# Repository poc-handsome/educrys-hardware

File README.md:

# educrys-hardware

Subfolders contain the documentation for [mechanical](/mechanical-design) (TODO) and [electronic](/electronic-design) (TODO) design of EduCrys setup for the users who want to build or adapt it by themselves.

The sections below provide information for users who have received a ready-to-use setup.

## Packing

While most electronic components of EduCrys are enclosed in a robust metallic box, many sensors and other parts need careful packing to avoid damage during transport. The pictures below show an example of such packing. The final package has dimensions of 60x41x23 cm and weight of 13.3 kg.

## Transport without packing

If the EduCrys setup is transported in the partly-assembled state, the following safety measures are recommended:

- Disconnect the rotation motor, detach the seed holder, wind the pulling wire on the main pulley and fix it with a tape
- Disconnect the camera and detach it from the magic arm
- Tape the crucible and camera cable to the main body to prevent motion
- Pack the seed holder and camera separately

## List of components

### Main components

- Main body with all connectors detached, except the camera cable, which is taped on the right wall. Two M6 screws are left in the profiles on both sides.
- Main stand with the pulling motor and weight cell. The pulling wire is wound and taped on the motor roll.
- Second stand with the fan and the small sensor box. The infrared sensor and LED should be protected with bubble wrap.
- Seed holder with a rotation motor in a bubble wrap bag. Small S-shaped hook to attach the seed holder to the pulling wire.
- Aluminum crucible with solid tin (99.9%), in a bubble wrap bag, should not move around in the transport box.

### Sensors and cables

- Raspberry Pi camera with a cover, attached to a magic arm, all inside a bubble wrap
- 1x PT100 and 2x thermocouple sensors with about 1.5 m wire length
- Raspberry Pi keyboard incl. USB cable and mouse, gamepad
- HDMI monitor cable, power cable

### Tools

- 30 cm metallic ruler
- Small spoon and small metal blow to be used when removing oxide layer
- 3 Inbus keys for seed holder, for opening main body, and for mounting both vertical profiles
- Nylon wire, which can be used temporarily if the steel wire of the seed holder breaks
- Warning sign for hot surfaces

### Raw material

- About 1 mm thick tin crystal, which can be used as seed
- About 1 mm thick copper wire, which can be used as seed
- (Tin pellets with 99.9% purity)

### Not included
- Protective glasses when working close to the crucible. **The hot liquid metal may splash if something falls into the melt!**
- Protective gloves when touching the hot crucible, for example, to adjust its position.
- Monitor
- Power strip

## Assembling the setup

### Mechanical

- Place the main body on a table with the logo on the front
- Attach the main stand on the left profile with a M6 screw, close to the front. Connect the motor and weight cell cables.
- Attach the fan stand on the right profile with a M6 screw, close to the back. Connect the fan and sensor cables.
- Guide the pulling wire over 3 pulleys from the pulling motor to the weight cell. Insert a hook in the loop at the wire end. Keep the wire tightened, otherwise it will unwind itself from the pulley on the motor axis.
- Hang the seed holder on the hook. The tilt of the seed holder should remain adjustable in two perpendicular directions.
- Attach the cable with two pins to the rotation motor. The polarity is not important. Keep the free length of this cable sufficient during the motion of the seed holder. This cable prevents the seed holder from rotating, but it should not pull it away from the vertical axis.
- Place the crucible on the hotplate. Check that the seed holder is in the middle of the crucible. Adjust the main stand position if necessary.

### Sensors and cables

- Attach the magic arm with camera on the right profile, close to the front. Carefully pull out the camera cable from the slit in the right wall. Insert the cable end into the connector at the back of the camera with the conducting pins towards the board. Push the black connector part upwards to fix the cable.
- Insert the PT100 sensor in a horizontal borehole and one thermocouple in a vertical borehole of the crucible. Both sensor cables should be bound together to prevent the PT100 sliding out of the hole. **This would lead to strong overheating of the crucible during temperature-controlled heating!**
- The second thermocouple could be used to measure ambient air, melt, or some parts inside the main body.
- Connect the keyboard with the red USB cable to the socket in the right wall. Connect the mouse and the gamepad to the keyboard. The USB ports in the keyboard can be also used to attach USB flash memory for data transfer.
- Connect a monitor to the HDMI socket in the right wall.
- Attach the power cable at the back of the main body. **Raspberry Pi starts as soon as power is connected! Always use the shutdown function in the Menu before disconnecting the power to avoid data loss.**
- If necessary, a network cable can be attached directly to the Raspberry Pi board through an opening in the back wall. Remove the screws and carefully pull the back wall for about 5 cm to access Raspberry Pi. **The network socket in the back wall can be only used for the sensor box.**

### Clock 

- Check the system clock after the log in. Newer EduCrys setups have a hardware clock with battery backup, while others rely on synchronization over network.
- The following steps are required to install an external hardware clock, see also [raspberry-pi-geek.de](https://www.raspberry-pi-geek.de/ausgaben/rpg/2015/03/echtzeituhr-modul-ds3231-sorgt-fuer-genaue-zeitangaben/2/) 
  - Update system time: `sudo date -s "19 May 2025 18:00:00" `
  - Attach the hardware clock to the I2C bus and find the address (e.g. 68): `sudo i2cdetect -y 1`
  - Configure the system to use the hardware clock (use the address from above) and add this line also to /etc/rc.local: `echo ds3231 0x68 | sudo tee /sys/class/i2c-adapter/i2c-1/new_device`
  - Synchronize the hardware clock with system time: `sudo hwclock -w`
  - Disable synchronization over network: `sudo update-rc.d ntp disable`   `sudo update-rc.d fake-hwclock disable`   `sudo timedatectl set-ntp false`

The final setup should look like this.

## Acknowledgements

[This project](https://poc-handsome.github.io/) has received funding from the European Research Council (ERC) under the 
European Union’s Horizon Europe framework programme for research and innovation (grant agreement No. 101122970).

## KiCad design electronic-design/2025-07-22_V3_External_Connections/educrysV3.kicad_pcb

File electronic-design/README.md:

## E01 PCB

### Layout of the PCB

Design files for KiCad (8.0.0) are here: [KiCad](https://github.com/poc-handsome/educrys-hardware/tree/main/electronic-design/E01/KiCad)

The following improvements have not been implemented yet:
- Separate pin header for the clock module
- Larger screw terminal for the connection between main PCB and sensor PCB
- Avoid risk of short circuit when soldering capacitors

### Soldering

Main PCB with soldered parts, top and bottom views:

Sensor PCB with soldered parts, top and bottom views:

Remarks:
- The connection between the main board and sensor board must be cut 
- For all screw terminals the holes are oriented to the rim of the board 
- A small 2 mm gap should be left between the 100 uF capacitor to avoid short circuit 
- Resitor values are not printed correctly on the board, use closes E12 values
- All flux residues should be cleaned from both board sides, e.g. using Kontaktchemie LR

### Modules

PCB after mounting the modules:

Remarks:

- First solder pin headers [E04H3] on the bottom of all modules [E03T2 etc.]. Make short breaks to avoid overheating the chip
- Solder screw terminals on the top of modules [E03T5, E03T2, E03W2, E03C]. The holes are oriented to the center of the board for [E03T5, E03W2] and to the rim of the board for [E03T2, E03C]
- Solder a female header on the top of the module [E03C] (4 pins on the left) and connect the module [E03D] there
- All flux residues should be cleaned from both board sides, e.g. using Kontaktchemie LR
- The modules will be fastened later to the PCB with a 10 mm spacer and two M2.5 screws. M3 screws are too big!

## E02 Wiring diagram

Schematic of the connections using the parts given below:

(pic)

Photo of the final wiring

(pic)

Remarks:

## E03 Devices: sensors, actuators

Prices are given per one piece in EUR incl. VAT. 

| Part  | Description                             | Use               | Price | Vendor/Link              | Datasheet | 
|-------|-----------------------------------------|-------------------|-------|--------------------------|-----------|
| E03H  | Hotplate, Severin KP 1092               | Crucible heating  | 27.99 | [Conrad/704233](https://www.conrad.de/de/p/severin-kp-1092-1092-kochplatte-704233.html?searchType=SearchRedirect)       |           |
| E03P1 | Stepper, Nema-17 1:20                   | Crystal pulling   | 56.90 | [Conrad/2355877](https://www.conrad.de/de/p/joy-it-schrittmotor-nema17-07gm-0-44-nm-1-68-a-wellen-durchmesser-8-mm-2355877.html?searchType=SearchRedirect)        |           |
| E03P2 | Motor driver IC, DRV8834                | Stepper motor     | 8.24  | [Exptech/80-2134](https://exp-tech.de/products/pololu-drv8834-low-voltage-stepper-motor-driver-carrier)     |           |
| E03R1 | DC motor 1000:1                         | Seed rotation     | 12.95 | [Conrad/1289388](https://www.conrad.de/de/p/sol-expert-g1000-micro-getriebemotor-g-1000-metallzahnraeder-1-1000-2-18-u-min-1289388.html?searchType=SearchRedirect)      |           |
| E03R2 | Motor driver IC, DRV8838                | DC motor          | 4.10  | [Exptech/80-2990](https://exp-tech.de/products/pololu-drv8838-single-brushed-dc-motor-driver-carrier)      |           |
| E03F1 | Fan, 120 mm, 5V                         | Crystal cooling   | 35.61 | [Conrad/816459971](https://www.conrad.de/de/p/noctua-nf-f12-5v-pwm-fan-1-pack-brun-120-mm5-v-pwm-0-75-w-0-15-a-93-4-816459971.html?searchType=SearchRedirect)    |           |
| E03W1 | Weight cell, 1 kg                       | Crystal weight    | 39.37 | [Conrad/2104290](https://www.conrad.de/de/p/sauter-ck-1-0p1-ck-1-0p1-messzelle-ck-p1-4-2104290.html?searchType=SearchRedirect)      |           |
| E03W2 | Weight cell driver IC, HX711            | Weight cell       | 9.86  | [Digikey/1568-1436-ND](https://www.digikey.de/de/products/detail/sparkfun-electronics/13879/6202732?s=N4IgTCBcDaIIwFYBsAOAtHALAZiWgcgCIgC6AvkA)     |           |
| E03T1 | Thermal sensor PT100, 3x150 mm, 500 °C  | Temperature sensor | 142.87 | [RS/397-1315](https://de.rs-online.com/web/p/widerstands-temperatursensoren/3971315?searchId=d1256e21-5988-4aaf-8b94-83c79a26ba8f)             |           |
| E03T2 | PT100 driver IC, MAX31865               | Temperature sensor | 12.82 | [Digikey/1528-3328-ND](https://www.digikey.de/de/products/detail/adafruit-industries-llc/3328/6562952)    |           |
| E03T4 | 2x Thermocouple, Type K, 1x250 mm, 750 °C | Temperature sensor | 47.36 | [RS/787-7706](https://de.rs-online.com/web/p/thermoelemente/7877706?searchId=9bbca203-3abb-4fba-a2c3-11345d2f288b)       |           |
| E03T5 | Thermocouple driver IC, MAX31856        | Temperature sensor | 17.98  | [Digikey/1528-1772-ND](https://www.digikey.de/de/products/detail/adafruit-industries-llc/3263/6227009?s=N4IgTCBcDaIIwFYwA4C0cDsGyoHIBEQBdAXyA)    |           |
| E03C  | Current sensor, INA219                  | Motor current     | 8.53   | [Digikey/1528-904-ND](https://www.digikey.de/de/products/detail/adafruit-industries-llc/904/5353628?s=N4IgTCBcDaIIwFYwA4C0BOADAFlQOQBEQBdAXyA)      |           |
| E03A  | Air sensor, SHT31                       | Air temperature, humidity | 11.96 | [Digikey/1528-2857-ND](https://www.digikey.de/de/products/detail/adafruit-industries-llc/2857/5804106?s=N4IgTCBcDaIIYBM4DMBOBXAlgFwAQGUAJAFQGYBGEAXQF8g) |           |
| E03I  | IR sensor, MLX90640                     | Hotplate temperature | 30.28 | [Digikey/MLX90640ESF-BAB-000-TU-ND](https://www.digikey.de/de/products/detail/melexis-technologies-nv/MLX90640ESF-BAB-000-TU/8638464?s=N4IgTCBcDaILIBkAaBOADANgCxoKIGUAxAWgCEBBU4tG4gFQFViA5AERAF0BfIA) |           |
| E03D  | Real time clock, DS3231                 | Raspberry Pi time backup | 15.0  | [Digikey/1528-3013-ND](https://www.digikey.de/de/products/detail/adafruit-industries-llc/3013/5875808) |           |
| E03O1 | RPi camera                              | Optical camera | 51.90 | [Welectron/RP3-102610](https://www.welectron.com/Offizielle-Raspberry-Pi-HQ-Camera)        |           |
| E03O2 | Camera lens 8-50 mm                     | Optical camera | 42.90 | [Welectron/WS9-018245](https://www.welectron.com/Waveshare-18245-8-50mm-Zoom-Lens-for-Pi)        |           |

## E04 Electrical components

Prices are given per one piece in EUR incl. VAT. In some cases SETS with a larger number of parts are given.

| Part  | Description                             | Use               | Price | Vendor/Link              | Datasheet | 
|-------|-----------------------------------------|-------------------|-------|--------------------------|-----------|
| E04S1 | 2x Power socket                         | SSR box           | 4.79  | [Conrad/2484787](https://www.conrad.de/de/p/as-schwabe-45084-einbau-steckdose-grau-2484787.html?searchType=SearchRedirect)  |  |
| E04S2 | Solid state relais                      | SSR box           | 74.52 | [RS/491-4947](https://de.rs-online.com/web/p/halbleiterrelais/4914947)  |  |
| E04R1 | Raspberry Pi 4 B (4 GB)                 |                   | 57.90 | [Welectron/RP1-141400](https://www.welectron.com/Raspberry-Pi-4-B-4-GB)  |  |
| E04R2 | SD card 64GB                            | Raspberry Pi      | 6.9   | [Welectron/SD1-200644](https://www.welectron.com/SanDisk-SDSQUAB-064G-GN6MA-Ultra-microSD-Speicherkarte-64-GB-140-MB-s)  |  |
| E04R3 | Heatsink                                | Raspberry Pi      | 1.3   | [Welectron/409151](https://www.welectron.com/Raspberry-Pi-Kuehlkoerpersatz)  |  |
| E04R4 | Power supply 5V, 3A                     | Raspberry Pi      | 7.5   | [Welectron/408024-012](https://www.welectron.com/Offizielles-Raspberry-Pi-4-Steckernetzteil-USB-C-51V-3A-weiss-EU)  |  |
| E04R5 | Keyboard + mouse                        | Raspberry Pi      | 27.90 | [Welectron/409483-002](https://www.welectron.com/Offizielle-Raspberry-Pi-Tastatur-Maus-Kombination-rot-weiss-DE)  |  |
| E04R6 | Gamepad                                 | Raspberry Pi      | 4.99  | [Conrad/1954771](https://www.conrad.de/de/p/joy-it-gamepad-snes-design-gamepad-raspberry-pi-universal-grau-1954771.html?searchType=SearchRedirect)  |  |
| E04E1 | SET: Metal film resistors               | PCB               | 46.65 | [Reichelt/METALL E 12](https://www.reichelt.de/de/de/shop/produkt/metallschichtwiderstandssortiment_e12-12049)  |  |
| E04E2 | SET: Foil capacitors                    | PCB               | 83.50 | [Reichelt/SORTIMENT 100](https://www.reichelt.de/de/de/shop/produkt/sortimentsbox_folienkondensatoren_rm_5mm-19263)  |  |
| E04E3 | 4x Capacitor 100 uF                     | PCB               | 1.29  | [Conrad/1179727](https://www.conrad.de/de/p/panasonic-16sepc100m-elektrolyt-kondensator-radial-bedrahtet-2-5-mm-100-f-16-v-dc-20-o-x-h-6-3-mm-x-6-mm-1-st-1179727.html)  |  |
| E04E4 | Buzzer                                  | PCB               | 0.99  | [Reichelt/KXG1205C](https://www.reichelt.de/de/de/shop/produkt/indikator_85db_2300_hz_5_v-360852)  |  |
| E04E5 | 2x Transistor KC337                     | PCB               | 0.02  | [Reichelt/BC 337-16](https://www.reichelt.de/de/de/shop/produkt/bipolartransistor_npn_45v_0_8a_0_625w_to-92-4985)  |  |
| E04E6 | White LED                               | Sensor box        | 0.5   | [Conrad/180754](https://www.conrad.de/de/p/nichia-nspw300ds-sel-b2v-w-led-bedrahtet-weiss-rund-3-mm-15000-mcd-20-20-ma-3-2-v-180754.html)  |  |
| E04H1 | 3x Female header precision, 2.54 mm, 1x36 | PCB             | 3.79  | [Conrad/733779-VQ](https://www.conrad.de/de/p/mpe-garry-buchsenleiste-praezision-anzahl-reihen-1-polzahl-je-reihe-36-115-1-036-0-mtf-xs0-1-1-st-733779.html)  |  | 
| E04H2 | 2x Female header precision, 2.54 mm, 2x10 | PCB             | 2.79  | [Conrad/733843-VQ](https://www.conrad.de/de/p/mpe-garry-buchsenleiste-praezision-anzahl-reihen-2-polzahl-je-reihe-10-115-3-020-0-mtf-xs0-1-st-733843.html)  |  |
| E04H3 | 2x Pin header, 2.54 mm, 1x50              | PCB             | 1.79  | [Conrad/734220-VQ](https://www.conrad.de/de/p/mpe-garry-stiftleiste-standard-anzahl-reihen-1-polzahl-je-reihe-50-087-1-050-0-s-xs0-1260-1-st-734220.html)  |  |
| E04T1 | Screw terminal, 2.54 mm, 2p               | PCB             | 0.34  | [Conrad/567588-83](https://www.conrad.de/de/p/ptr-hartmann-50692020021e-schraubklemmblock-0-75-mm-polzahl-2-gruen-1-st-567588.html)  |  |
| E04T2 | Screw terminal, 2.54 mm, 4p               | PCB             | 0.68  | [Conrad/567658-83](https://www.conrad.de/de/p/ptr-hartmann-50692040021e-schraubklemmblock-0-75-mm-polzahl-4-gruen-1-st-567658.html)  |  |
| E04T3 | 2x Screw terminal, 2.54 mm, 6p            | PCB             | 0.96  | [Conrad/567757-83](https://www.conrad.de/de/p/ptr-hartmann-50692060021e-schraubklemmblock-0-75-mm-polzahl-6-gruen-1-st-567757.html)  |  |
| E04T4 | 4x Screw terminal, 3.5 mm, 2p             | PCB             | 0.57  | [Conrad/732295-83](https://www.conrad.de/de/p/ptr-hartmann-50602020021f-schraubklemmblock-1-00-mm-polzahl-2-gruen-1-st-732295.html)  |  |
| E04T5 | Screw terminal, 5.08 mm, 2p               | PCB             | 0.19  | [Conrad/731877-83](https://www.conrad.de/de/p/ptr-hartmann-50500020134g-schraubklemmblock-1-50-mm-polzahl-2-grau-1-st-731877.html)  |  |
| E04T6 | Screw terminal, 5.08 mm, 3p               | PCB             | 0.29  | [Conrad/731891-83](https://www.conrad.de/de/p/ptr-hartmann-50500030134g-schraubklemmblock-1-50-mm-polzahl-3-grau-1-st-731891.html)  |  |
| E04T7 | Screw terminal, 5.08 mm, 4p               | PCB             | 0.39  | [Conrad/731908-83](https://www.conrad.de/de/p/ptr-hartmann-50500040134g-schraubklemmblock-1-50-mm-polzahl-4-grau-1-st-731908.html)  |  |
| E04J1 | 2x Jumper                                 | PCB             | 0.05  | [Reichelt/MPE 149-1-002-F0](https://www.reichelt.de/de/de/shop/produkt/jumper_2_54_mm_geoeffnet_schwarz-119941)  |  |

## E05 Connectors

Prices are given per one piece in EUR incl. VAT. 

| Part  | Description                             | Use               | Price | Vendor/Link              | Datasheet | 
|-------|-----------------------------------------|-------------------|-------|--------------------------|-----------|
| E05P1 | Power socket with fuse, 10A, C14        | Power cable       | 3.29  | [Conrad/2522092](https://www.conrad.de/de/p/tru-components-tc-10088368-kaltgeraete-steckverbinder-c14-stecker-einbau-vertikal-gesamtpolzahl-3-10-a-schwarz-1-st-2522092.html)           |           |
| E05P2 | Fuse (250V, 8A, Flink)                  | Power socken      | 0.18  | [Conrad/524207](https://www.conrad.de/de/p/eska-520-526-520526-feinsicherung-o-x-l-5-mm-x-20-mm-8-a-250-v-flink-f-inhalt-10-st-524207.html?searchType=SearchRedirect)        |           |
| E05M1 | Socket SUB-D-9                          | Motors            | 0.34  | [Conrad/1389963](https://www.conrad.de/de/p/connfly-ds1033-09fbnsiss-ct-d-sub-buchse-180-polzahl-9-loeten-1-st-1389963.html?searchType=SearchRedirect)           |           |
| E05M2 | Jack SUB-D-9                            | Motors            | 1.95  | [Reichelt/MHDTZK 9 S](https://www.reichelt.de/de/de/shop/produkt/d-sub_stecker_9_polig-342366)      |           |
| E05M3 | 2x SUB-D screws                         | Motors            | 0.63  | [Digikey/609-1421-ND](https://www.digikey.de/de/products/detail/amphenol-cs-fci/863001061TLF/1001735)      |           |
| E05T1 | 2x Socket, Type-K                       | Thermocouple      | 4.79  | [Conrad/121365-VQ](https://www.conrad.de/de/p/b-b-thermo-technik-0220-0005-miniaturdose-typ-k-gelb-50-120-c-gelb-inhalt-1-st-121365.html?searchType=SearchRedirect)            |           |
| E05T2 | 2x Jack, Type-K                         | Thermocouple      | 3.79  | [Conrad/133523-VQ](https://www.conrad.de/de/p/b-b-thermo-technik-0220-0001-miniaturstecker-typ-k-gelb-gelb-inhalt-1-st-133523.html?searchType=SearchRedirect)            |           |
| E05S1 | Socket, DIN-6                           | PT sensor         | 5.49  | [Conrad/733449-VQ](https://www.conrad.de/de/p/lumberg-0103-06-din-rundsteckverbinder-flanschbuchse-kontakte-gerade-polzahl-6-silber-1-st-733449.html?searchType=SearchRedirect)            |           |
| E05S2 | Jack, DIN-6                             | PT sensor         | 5.99  | [Conrad/733336](https://www.conrad.de/de/p/lumberg-0131-06-din-rundsteckverbinder-stecker-gerade-polzahl-6-silber-1-st-733336.html?searchType=SearchRedirect)            |           |
| E05W1 | Socket, M8, 09-3390-80-04               | Weight cell       | 12.90 | [Conrad/733875](https://www.conrad.de/de/p/binder-09-3390-80-04-sensor-aktor-einbausteckverbinder-m8-buchse-gerade-polzahl-sensoren-4-1-st-733875.html?searchType=SearchRedirect)            |           |
| E05W2 | Jack, M8, 99-3383-00-04                 | Weight cell       | 13.99 | [Conard/746035](https://www.conrad.de/de/p/binder-99-3383-00-04-sensor-aktor-steckverbinder-unkonfektioniert-m8-stecker-gerade-polzahl-sensoren-4-1-st-746035.html?searchType=SearchRedirect)            |           |
| E05N1 | Socket, RJ45                            | Sensor box        | 5.99  | [Conrad/1497957](https://www.conrad.de/de/p/tru-components-rj-45-einbaubuchse-93038c234-1-st-1497957.html?searchType=SearchRedirect)           |           |
| E05H  | Feedthrough HDMI                        | Monitor	          | 9.75  | [Conrad/2473497](https://www.conrad.de/de/p/fm-slim-ft-hdmi-f-f-3-2-hole-adapter-einbau-cp30600gx1-cliff-inhalt-1-st-2473497.html?searchType=SearchRedirect)           |           |
| E05U  | Feedthrough USB                         | Keyboard          | 7.49  | [Conrad/2354829](https://www.conrad.de/de/p/adapter-buchse-einbau-usb-buchse-typ-a-usb-buchse-typ-b-cp30609n-cliff-inhalt-1-st-2354829.html?searchType=SearchRedirect)           |           |

## E06 Cables

Prices are given per one piece in EUR incl. VAT. 

| Part  | Description                             | Use               | Price | Vendor/Link              | Datasheet | 
|-------|-----------------------------------------|-------------------|-------|--------------------------|-----------|
| E06P	| Power cable C13, 10A / plug,	1.5 m     | C14 power socket  | 3.49  | [Conrad/2521347](https://www.conrad.de/de/p/sygonix-sy-5042694-kaltgeraete-anschlusskabel-schwarz-1-50-m-2521347.html?searchType=SearchRedirect)           |           |
| E06U2	| USB Kabel	Type-A / Micro-B, 1 m         | Wall to keyboard  | 1.9   | [Welectron/RP9-205570](https://www.welectron.com/Offizielles-Raspberry-Pi-micro-USB-Kabel)     |           |
| E06C	| RPi camera cable, 0.5 m                 | RPi to camera     | 2.9   | [Welectron/GM7-210500](https://www.welectron.com/Groundmicro-FPC-Kabel-100mm-Pitch-15-Pin-fuer-Raspberry-Pi-CSI-DSI-50-cm)     |           |
| E06H	| HDMI cable Type-A / Micro-D, 0.5 m      | RPi to wall       | 1.9   | [Welectron/GB1-053780](https://www.welectron.com/Goobay-53780-micro-HDMI-Kabel-HDMI-20-050m)     |           |
| E06U1	| USB cable Type-A / Type-B 90 deg, 0.5 m | RPi to wall       | 1.39  |	[Welectron/GB1-093016](https://www.welectron.com/Goobay-93016-USB-B-Kabel-gewinkelt-USB-20-050m)     |           |

## E07 Wiring

### Order list 

Prices are given in EUR incl. VAT. Typically a higher amount of materials is given than needed for 1 device.

| Nr | Description                      | Amount | Price | Vendor/Link              | Datasheet | 
|----|----------------------------------|--------|-------|--------------------------|-----------|
| 10 | Brown wire, 1.5 mm2              | 10 m   | 4.5   | [Reichelt/H07VK 1,5-10BR](https://www.reichelt.de/de/de/shop/produkt/schaltlitze_h07v-k_1_5_mm_10_m_braun-69505)  |           |
| 11 | Blue wire, 1.5 mm2               | 10 m   | 4.5   | [Reichelt/H07VK 1,5-10BL](https://www.reichelt.de/de/de/shop/produkt/schaltlitze_h07v-k_1_5_mm_10_m_blau-69504)  |           |
| 12 | Green-yellow wire, 1.5 mm2       | 10 m   | 4.5   | [Reichelt/H07VK 1,5-10GG](https://www.reichelt.de/de/de/shop/produkt/schaltlitze_h07v-k_1_5_mm_10_m_gruen_gelb-69506)  |           |
| 13 | Wire set, 0.25 mm2               | 1      | 27.99 | [Conrad/2201407](https://www.conrad.de/de/p/quadrios-19011ca085-litze-lify-1-x-0-25-mm-blau-braun-grau-rot-schwarz-weiss-gelb-gruen-70-m-2201407.html?searchType=SearchRedirect)           |           |
| 14 | Cable, 6 x 0.25 mm2              | 5 m    | 19.95 | [Conrad/486478](https://www.conrad.de/de/p/kabeltronik-liyy-steuerleitung-6-x-0-25-mm-grau-10602500-meterware-486478.html?searchType=SearchRedirect)            |           |
| 15 | Cable, 4 x 0.14 mm2              | 25 m   | 17.40 | [Reichelt/LIYCY 04-25](https://www.reichelt.de/de/de/shop/produkt/steuerleitung_4x0_14mm_geschirmt_25m-ring-10302)     |           |
| 16 | Compensation wire, 4 x 0.14 mm2  | 5 m    | 17.45 | [Conrad/121329](https://www.conrad.de/de/p/b-b-thermo-technik-ausgleichsleitung-0230-0191-messbereich-temperatur-10-bis-105-c-121329.html?searchType=SearchRedirect)            |           |
| 17 | Network cable                    | 5      | 4.95  | [Conrad/2521890](https://www.conrad.de/de/p/renkforce-rf-5043780-rj45-netzwerkkabel-patchkabel-cat-5e-u-utp-2-00-m-weiss-mit-rastnasenschutz-1-st-2521890.html?searchType=SearchRedirect)           |           |
| 18 | Fan extenstion cable             | 3      | 16.47 | [Conrad/976188](https://www.conrad.de/de/p/pc-luefter-verlaengerungskabel-1x-pc-luefter-stecker-4pol-1x-pc-luefter-buchse-4pol-0-30-m-schwarz-akasa-976188.html?searchType=SearchRedirect)           |           |
| 19 | Wire set, 0.34 mm2               | 1      | 49.95 | [Eckstein/SF11367](https://eckstein-shop.de/SparkFunHook-UpWire-AssortmentSolidCore2C22AWG)         |           |
| 20 | Blank ferrule set                | 1      | 8.99  | [Conrad/2870591](https://www.conrad.de/de/p/quadrios-22c485-aderendhuelsen-sortiment-unisoliert-1000-st-2870591.html?searchType=SearchRedirect)           |           |
| 21 | Receptable, 4.75 mm              | 10     | 1.9   | [Reichelt/FSH-M1 4.75](https://www.reichelt.de/de/de/shop/produkt/flachsteckhuelse_nicht_isoliert_breite_4_75mm-24854)     |           |
| 22 | Insulation sleeve (from set)     | 1      | 9.1   | [Reichelt/QUAD 1908C181](https://www.reichelt.de/de/de/shop/produkt/flachstecker-huelsen_set_0_5_x_4_8_mm_0_5_-1_5_mm_100-teilig-280155)   |           |
| 23 | Ring cable lug, M6               | 10     | 0.8   | [Reichelt/RK-B-6](https://www.reichelt.de/de/de/shop/produkt/ring-kerbschuhe_fuer_m6_blau-15254)          |           |
| 24 | Ring cable lug, M4               | 10     | 1.3   | [Reichelt/VT RK-B-4](https://www.reichelt.de/de/de/shop/produkt/ring-kerbschuhe_fuer_m4_blau-231385)       |           |
| 25 | Insulated ferrule set            | 3      | 14.97 | [Conrad/2870580](https://www.conrad.de/de/p/quadrios-2010c392-aderendhuelsen-sortiment-teilisoliert-200-st-2870580.html?searchType=SearchRedirect)           |           |
| 26 | Heat shrink tube set             | 1      | 23.99 | [Conrad/2583933](https://www.conrad.de/de/p/quadrios-1807ca006-schrumpfschlauchsortiment-schwarz-schrumpfrate-3-1-1-set-2583933.html?searchType=SearchRedirect)           |           |

**Sum = 211.31 EUR**

### Parts

These must be built using the items (Nr) from the order list.

| Part  | Description            | Amount | Wire                        | Length      | Ends                                                 |
|-------|------------------------|--------|-----------------------------|-------------|------------------------------------------------------|
| E07S1 | SSR box/phase          | 2      | 10: brown, 1.5 mm2          | 75 mm       | 20: blank ferrule / 20: blank ferrule                |
| E07S2 | SSR box/neutral        | 1      | 11: blue, 1.5 mm2           | 200 mm      | 20: blank ferrule / 20: blank ferrule                |
| E07S3 | SSR box/ground         | 1      | 12: green-yellow, 1.5 mm2   | 150 mm      | 20: blank ferrule / 20: blank ferrule                |
| E07S4 | SSR box/supply/phase   | 1      | 10: brown, 1.5 mm2          | 250 mm      | 20: blank ferrule / 21: receptacle + 22: sleeve      |
| E07S5 | SSR box/supply/neutral | 1      | 11: blue, 1.5 mm2           | 250 mm      | 20: blank ferrule / 21: receptacle + 22: sleeve      |
| E07S6 | SSR box/supply/ground  | 1      | 12: green-yellow, 1.5 mm2   | 250 mm      | 20: blank ferrule / 23: cable lug                    |
| E07S7 | supply/ground/top      | 1      | 12: green-yellow, 1.5 mm2   | 250 mm      | 23: cable lug / 24: cable lug                        |
| E07S8 | supply/ground/back     | 1      | 12: green-yellow, 1.5 mm2   | 150 mm      | 23: cable lug / 21: receptacle + 22: sleeve          |
| E07S9 | SSR box/signal         | 1      | 13: brown+grey, 0.25 mm2    | 210 mm      | 25: isolated ferrule / 25: isolated ferrule          |

| Part  | Description            | Amount | Wire                        | Length      | Ends                                                 |
|-------|------------------------|--------|-----------------------------|-------------|------------------------------------------------------|
| E07M1 | Motors/inside          | 1      | 14: 6 x 0.25 mm2, no shield | 200 mm      | solder + 26: heat shrink tube / 25: isolated ferrule |
| E07M2 | Motors/outside         | 1      | 14: 6 x 0.25 mm2            | 800 mm      | solder / solder + 26: heat shrink tube               |
| E07M3 | Motor/DC               | 1      | XX: 2 x 0.14 mm2            | 800 mm      | solder + 26: heat shrink tube / ..                   |
| E07P1 | PT/inside              | 1      | 15: 4 x 0.14 mm2, no shield | 280 mm      | solder + 26: heat shrink tube / 25: isolated ferrule |
| E07T1 | TC/inside              | 2      | 16: 2 x 0.14 mm2            | 300 mm      | none / 25: isolated ferrule                          |
| E07W1 | Weight/inside          | 1      | 15: 4 x 0.14 mm2, no shield | 300 mm      | solder + 26: heat shrink tube / 25: isolated ferrule |
| E07W2 | Weight/outside         | 1      | 15: 4 x 0.14 mm2            | 1100 mm     | solder / solder + 26: heat shrink tube               |
| E07B1 | Sensor box/inside      | 1      | 17: 8 x 0.14 mm2, no shield | 280 mm      | solder + 26: heat shrink tube / 25: isolated ferrule |
| E07B2 | Sensor box/outside     | 1      | 17: 8 x 0.14 mm2            | 900 mm      | none / 25: isolated ferrule                          |
| E07F1 | Fan/inside             | 1      | 18: 3 x 0.14 mm2            | 150 mm      | none / 25: isolated ferrule                          |
| E07Z1 | Zummer/inside          | 1      | 19: 2 x 0.34 mm2, solid     | 50 mm       | none / solder + 26: heat shrink tube                 |
| E07I2 | IR sensor/outside      | 1      | 19: 4 x 0.34 mm2, solid     | 100 mm      | none / solder + 26: heat shrink tube                 |
| E07L2 | LED/outside            | 1      | 19: 2 x 0.34 mm2, solid     | 400 mm      | none / solder + 26: heat shrink tube                 |
| E07R1 | RPi/5V                 | 1      | 19: 2 x 0.34 mm2, solid     | 45 mm       | none / none                                          |
| E07R2 | RPi/3.3V               | 1      | 19: 1 x 0.34 mm2, solid     | 30 mm       | none / none                                          |

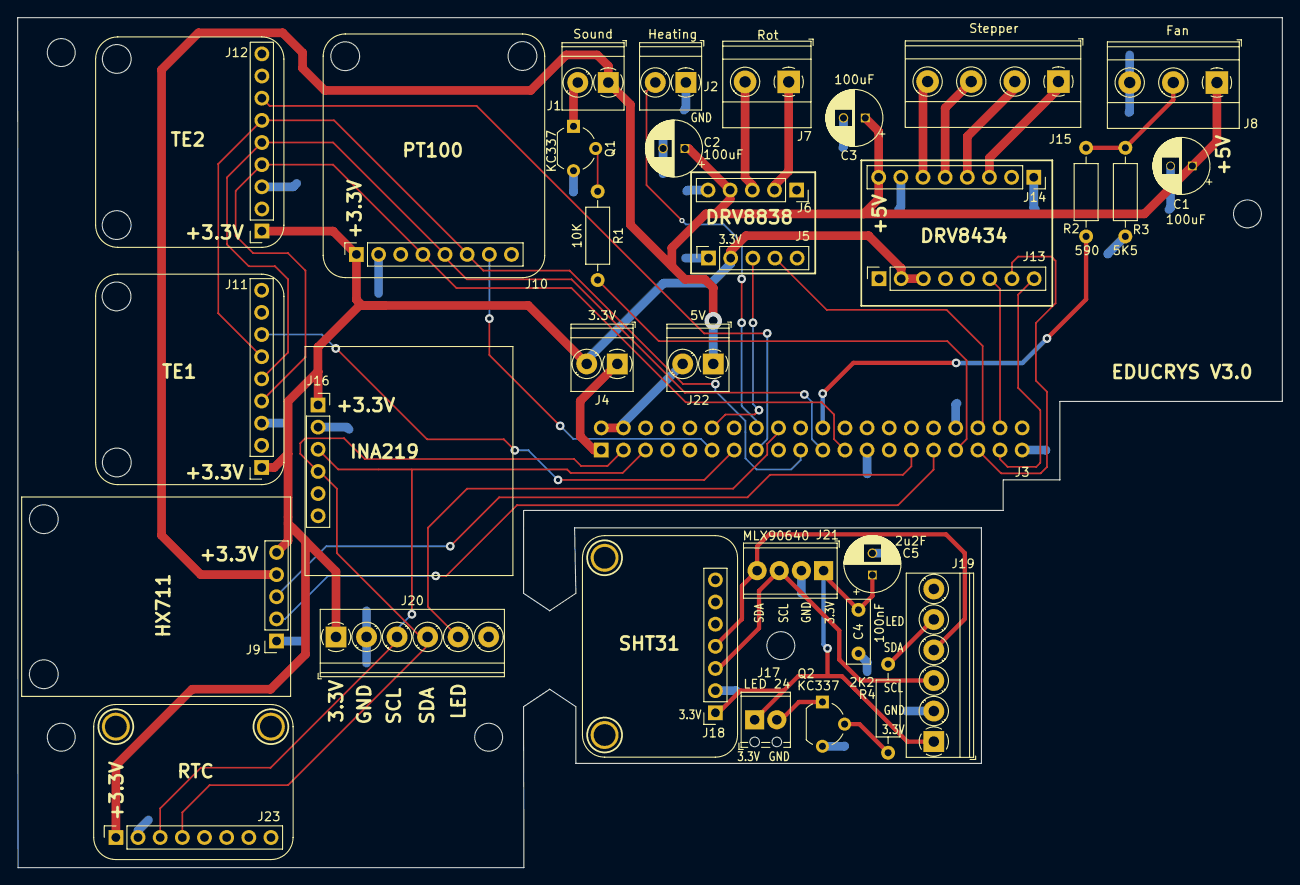
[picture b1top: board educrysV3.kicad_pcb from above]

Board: 2 copper layers, 145.0 x 97.5 mm, 51 parts (1 on the bottom side), 40 nets.

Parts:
C1, C2, C3: 100uF; CP_Radial_D6.3mm_P2.50mm
C4: 100nF; C_Rect_L7.2mm_W2.5mm_P5.00mm_FKS2_FKP2_MKS2_MKP2
C5: 2u2F; CP_Radial_D6.3mm_P2.50mm
H1, H2, H3, H4, H5: MountingHole; MountingHole_3.2mm_M3_DIN965
J1: Sound; TerminalBlock_Phoenix_PT-1,5-2-3.5-H_1x02_P3.50mm_Horizontal
J2: Heating; TerminalBlock_Phoenix_PT-1,5-2-3.5-H_1x02_P3.50mm_Horizontal
J3: RaspberryPi4B; PinSocket_2x20_P2.54mm_Vertical
J4: 3.3V; TerminalBlock_Phoenix_PT-1,5-2-3.5-H_1x02_P3.50mm_Horizontal
J5: DRV8838_Left; PinSocket_1x05_P2.54mm_Vertical
J6: DRV8838_Right; PinSocket_1x05_P2.54mm_Vertical
J7: Rot; TerminalBlock_Phoenix_MKDS-1,5-2_1x02_P5.00mm_Horizontal
J8: Fan; TerminalBlock_Phoenix_MKDS-1,5-3_1x03_P5.00mm_Horizontal
J9: HX711; PinSocket_1x05_P2.54mm_Vertical
J10: PT100; PinSocket_1x08_P2.54mm_Vertical
J11: TE1; PinSocket_1x09_P2.54mm_Vertical
J12: TE2; PinSocket_1x09_P2.54mm_Vertical
J13: DRV8434_Left; PinSocket_1x08_P2.54mm_Vertical
J14: DRV8434_Right; PinSocket_1x08_P2.54mm_Vertical
J15: Stepper; TerminalBlock_Phoenix_MKDS-1,5-4_1x04_P5.00mm_Horizontal
J16: INA219; PinSocket_1x06_P2.54mm_Vertical
J17: LED 24; TerminalBlock_Phoenix_MPT-0,5-2-2.54_1x02_P2.54mm_Horizontal
J18: SHT31; PinSocket_1x07_P2.54mm_Vertical
J19: ToMain; TerminalBlock_Phoenix_PT-1,5-6-3.5-H_1x06_P3.50mm_Horizontal
J20: ToExt; TerminalBlock_Phoenix_PT-1,5-6-3.5-H_1x06_P3.50mm_Horizontal
J21: MLX90640; TerminalBlock_Phoenix_MPT-0,5-4-2.54_1x04_P2.54mm_Horizontal
J22: 5V; TerminalBlock_Phoenix_PT-1,5-2-3.5-H_1x02_P3.50mm_Horizontal
J23: RTC; PinSocket_1x08_P2.54mm_Vertical
Q1, Q2: KC337; TO-92_Wide
R1: 10K; R_Axial_DIN0207_L6.3mm_D2.5mm_P10.16mm_Horizontal
R2: 590; R_Axial_DIN0207_L6.3mm_D2.5mm_P10.16mm_Horizontal
R3: 5K5; R_Axial_DIN0207_L6.3mm_D2.5mm_P10.16mm_Horizontal
R4: 2K2; R_Axial_DIN0207_L6.3mm_D2.5mm_P10.16mm_Horizontal
STANDOFF1, STANDOFF3, STANDOFF3#2, STANDOFF3#3, STANDOFF3#4, STANDOFF3#5, STANDOFF3#6, STANDOFF3#7: STAND-OFF
U$6, U$7, U$19, U$20: MOUNTINGHOLE2.5; MOUNTINGHOLE_2.5_PLATED

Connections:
+3.3V: J4.2, J5.2, J9.5, J10.1, J11.1, J12.1, J13.2, J13.3, J16.1, J20.1, J23.1
+3.3V_EXT: C4.1, C5.1, J17.1, J18.1, J19.1, J21.1
+3.3V_LowEnd: J3.1, J4.1
+5V: C1.1, C2.1, C3.1, J1.1, J6.4, J8.1, J9.4, J14.8, J22.1
+5V_LowEnd: J3.2, J3.4, J22.2
FAN_PWM 25: J3.22, R2.2
GND: C1.2, C2.2, C3.2, J2.1, J3.25, J3.34, J3.39, J5.1, J6.5, J8.3, J9.1, J10.2, J11.3, J12.3, J14.1, J14.7, J16.2, J20.2, J23.2, Q1.3 (E), R3.1
GND_EXT: C4.2, C5.2, J18.2, J19.2, J21.2, Q2.3 (E)
LED 24: J3.18, J20.5
LED 24_EXT: J19.5, R4.1
LIN_DIR 16: J3.37, J13.8
LIN_ON 20: J3.38, J13.6
LIN_PWM 19: J3.35, J13.7
unnamed: J1.2, Q1.1 (C)
unnamed: J6.2, J7.1
unnamed: J6.3, J7.2
unnamed: J8.2, R2.1, R3.2
unnamed: J14.3, J15.1
unnamed: J14.4, J15.2
unnamed: J14.5, J15.3
unnamed: J14.6, J15.4
unnamed: J17.2, Q2.1 (C)
unnamed: Q1.2 (B), R1.1
unnamed: Q2.2 (B), R4.2
PT100_CS 17: J3.11, J10.7
ROT_DIR 16: J3.36, J5.4
ROT_PWM 18: J3.12, J5.3
SCL 3: J3.5, J16.3, J20.3, J23.3
SCL 3_EXT: J18.3, J19.3, J21.3
SDA 2: J3.3, J16.4, J20.4, J23.4
SDA 2_EXT: J18.4, J19.4, J21.4
SOUND 13: J3.33, R1.2
SSR 23: J2.2, J3.16
TE1_CS 27: J3.13, J11.7
TE2_CS 22: J3.15, J12.7
T_CLK 11: J3.23, J10.4, J11.4, J12.4
T_SDI 9: J3.21, J10.5, J11.5, J12.5
T_SDI 10: J3.19, J10.6, J11.6, J12.6
W_CLK 6: J3.31, J9.2
W_DAT 5: J3.29, J9.3

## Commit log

2025-05-22 Add description
2025-05-22 Add transport instructions
2025-10-20 Revert "Uploaded files"
2025-10-20 Update wiring
2026-01-22 Update electronic documentation
